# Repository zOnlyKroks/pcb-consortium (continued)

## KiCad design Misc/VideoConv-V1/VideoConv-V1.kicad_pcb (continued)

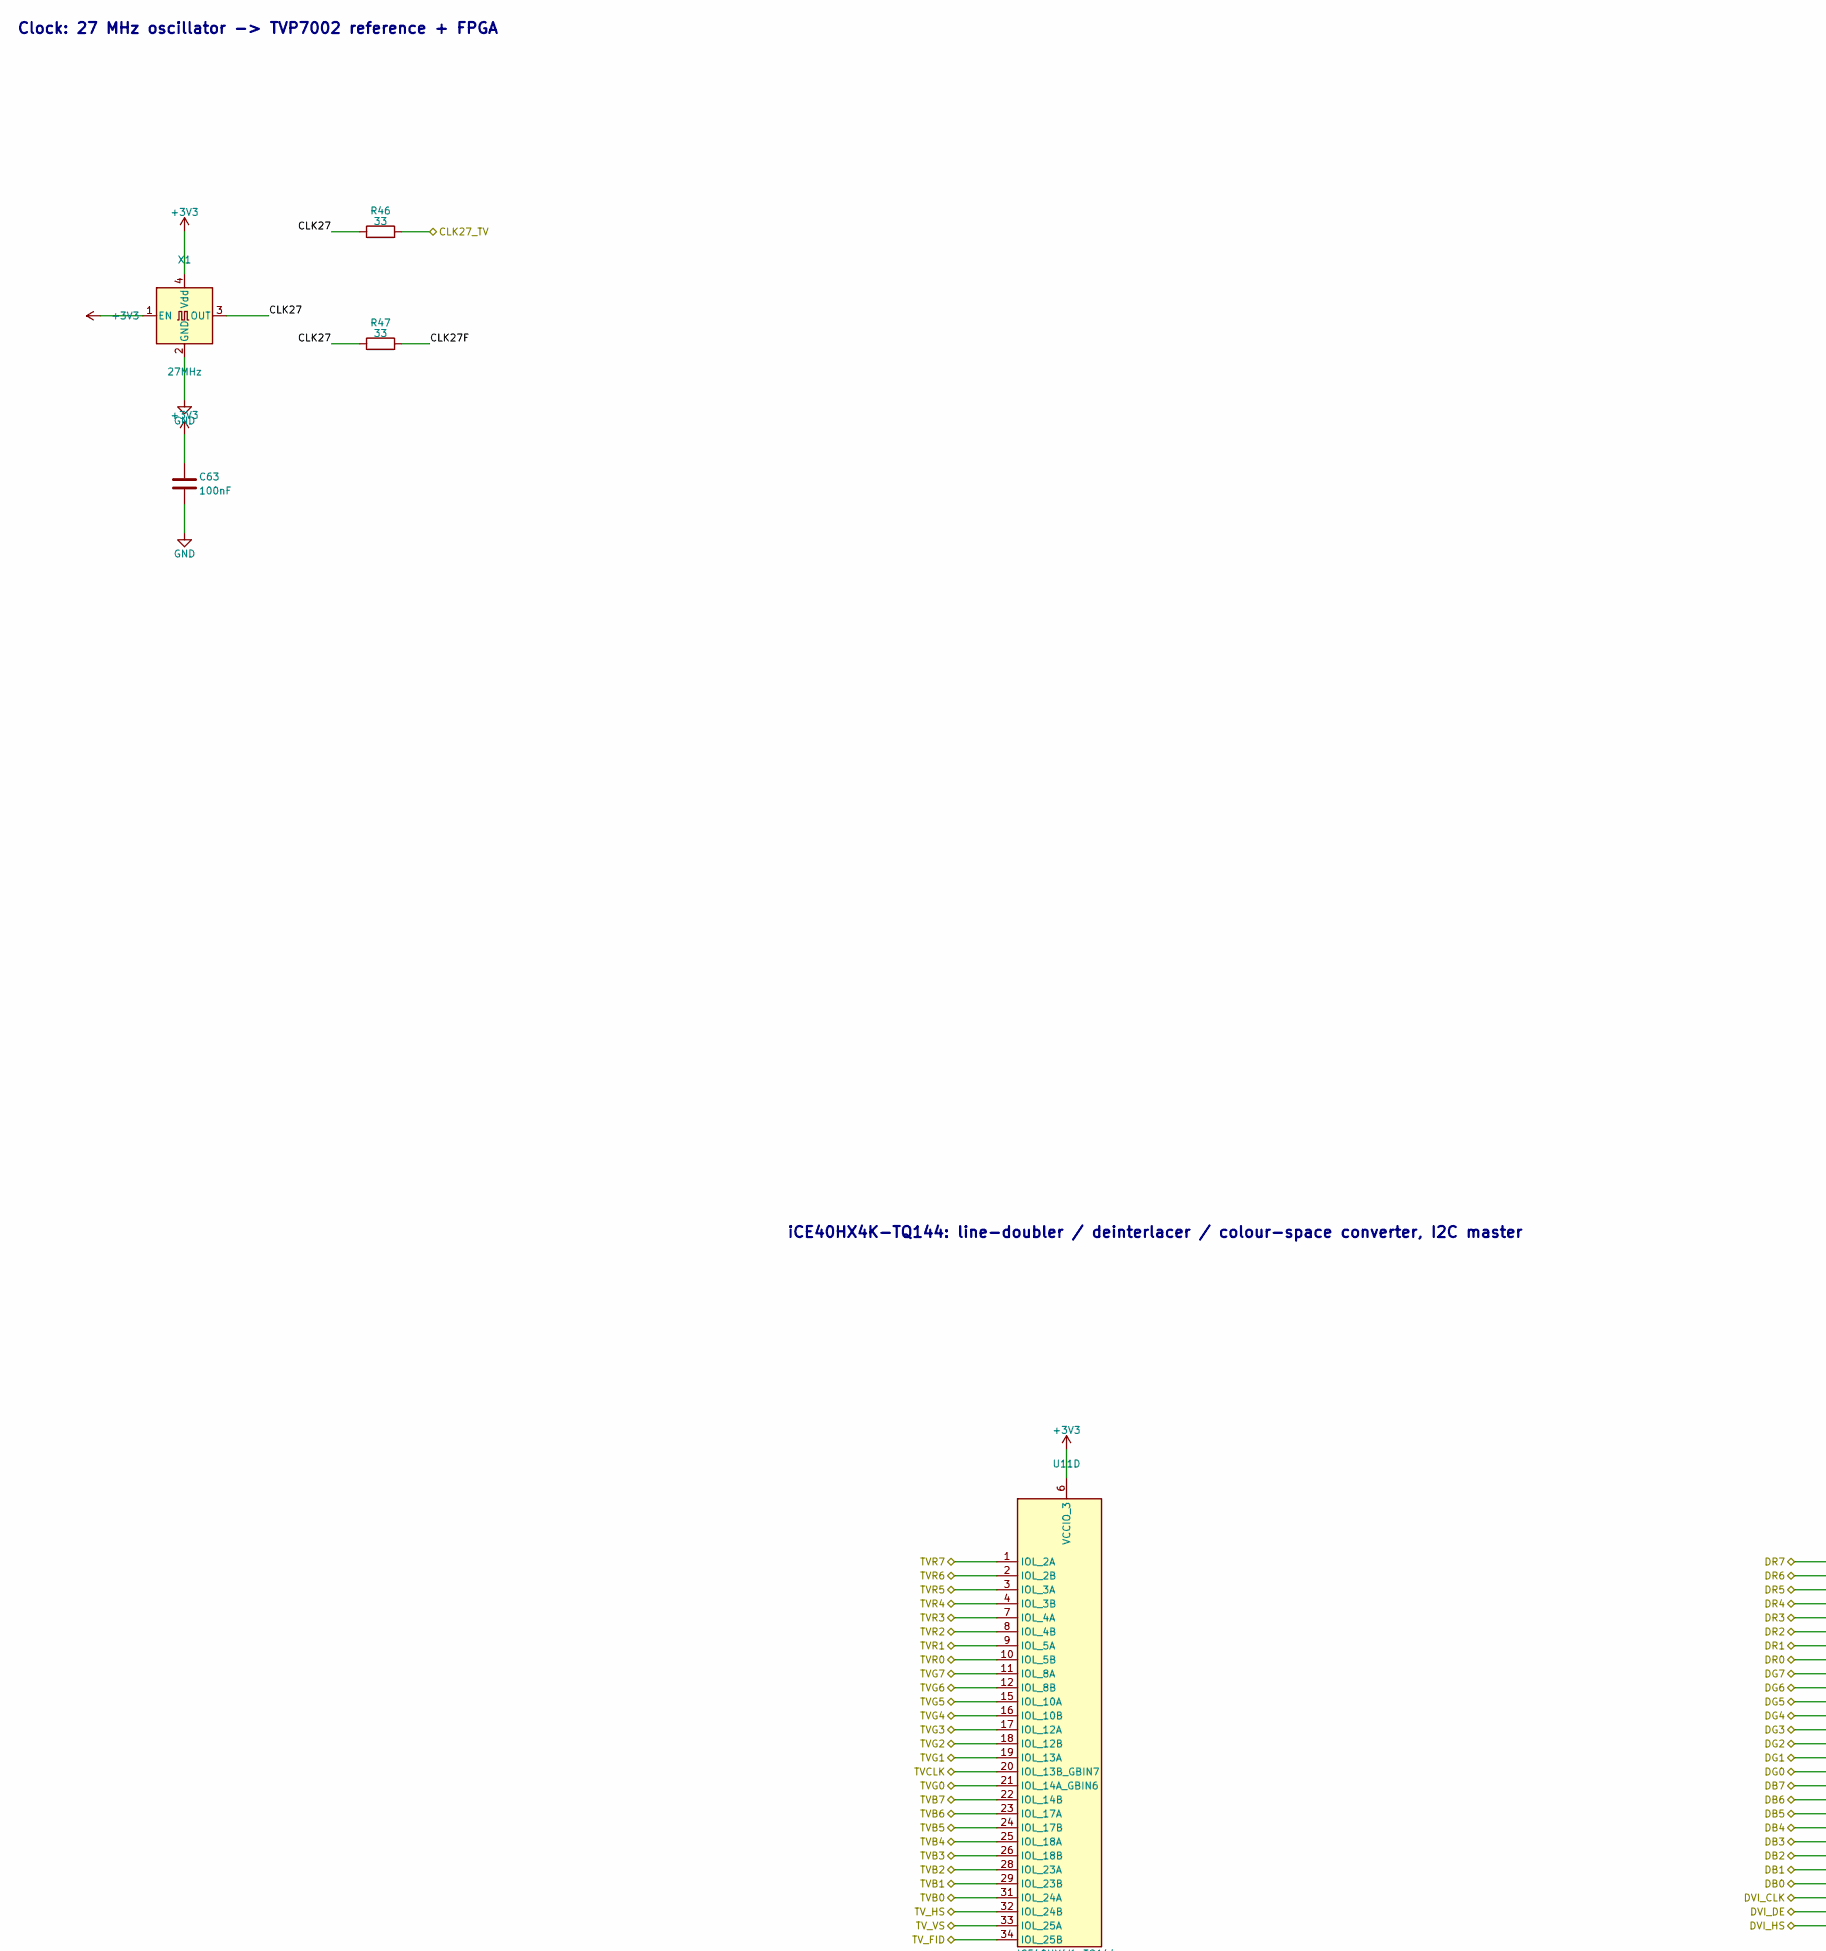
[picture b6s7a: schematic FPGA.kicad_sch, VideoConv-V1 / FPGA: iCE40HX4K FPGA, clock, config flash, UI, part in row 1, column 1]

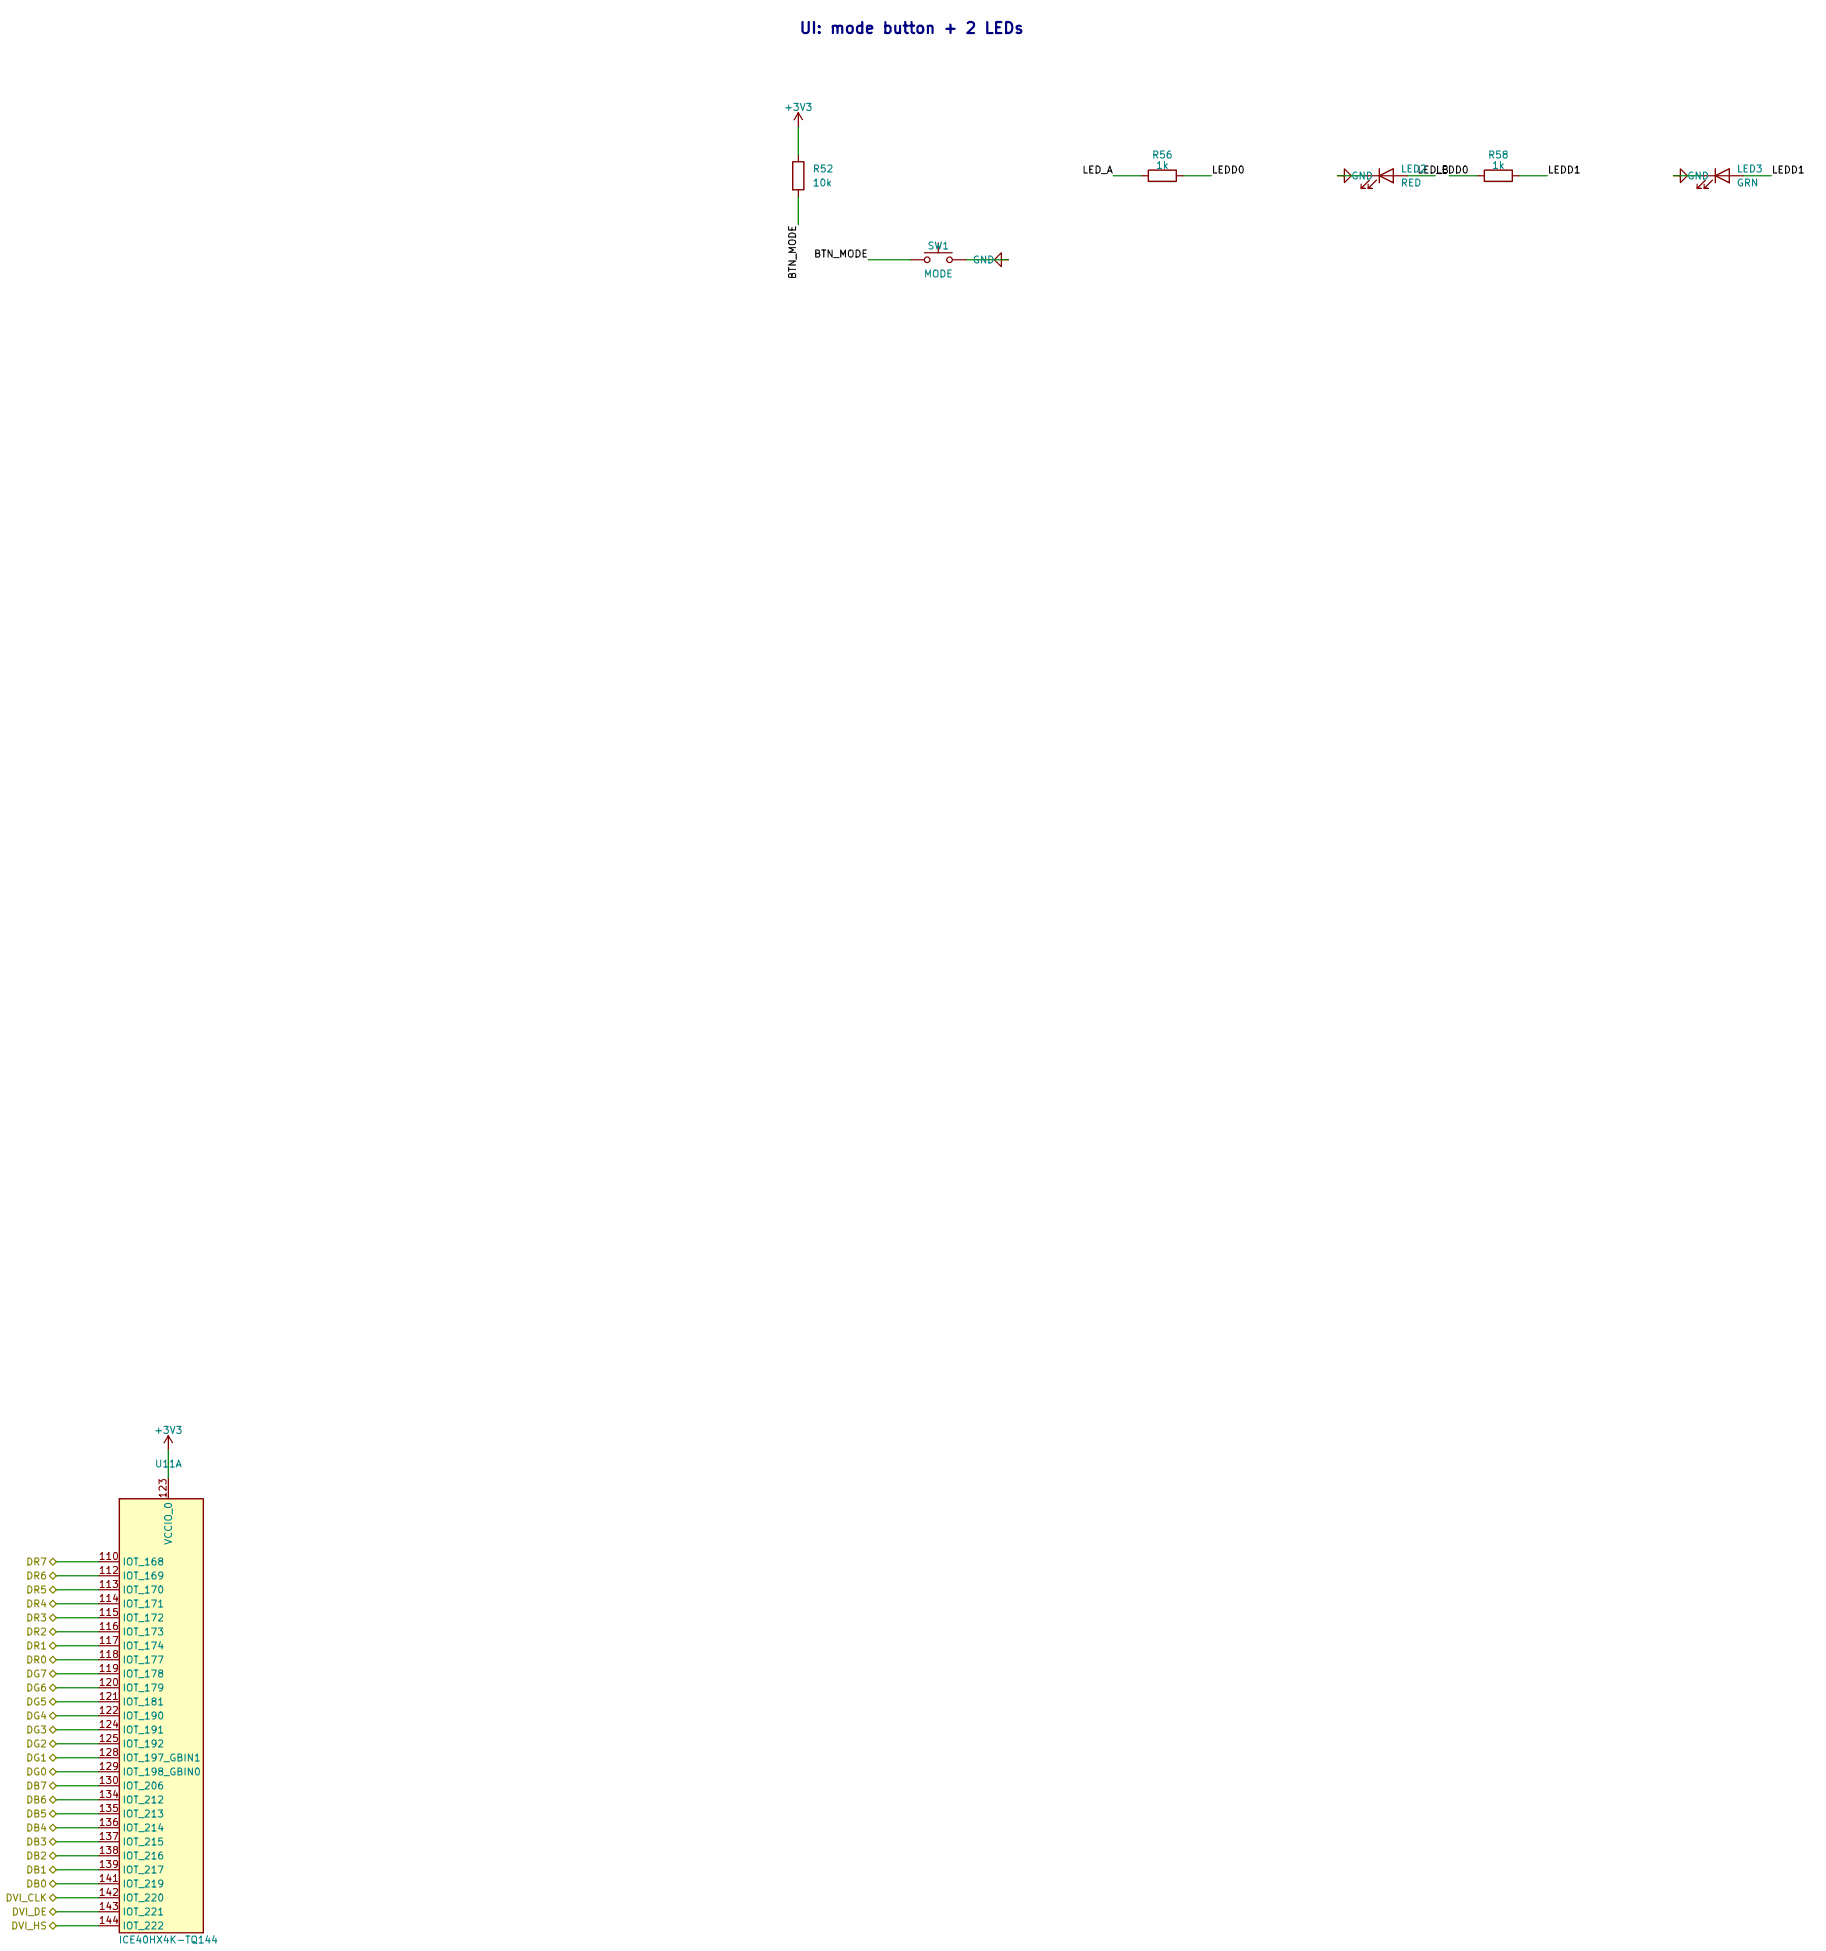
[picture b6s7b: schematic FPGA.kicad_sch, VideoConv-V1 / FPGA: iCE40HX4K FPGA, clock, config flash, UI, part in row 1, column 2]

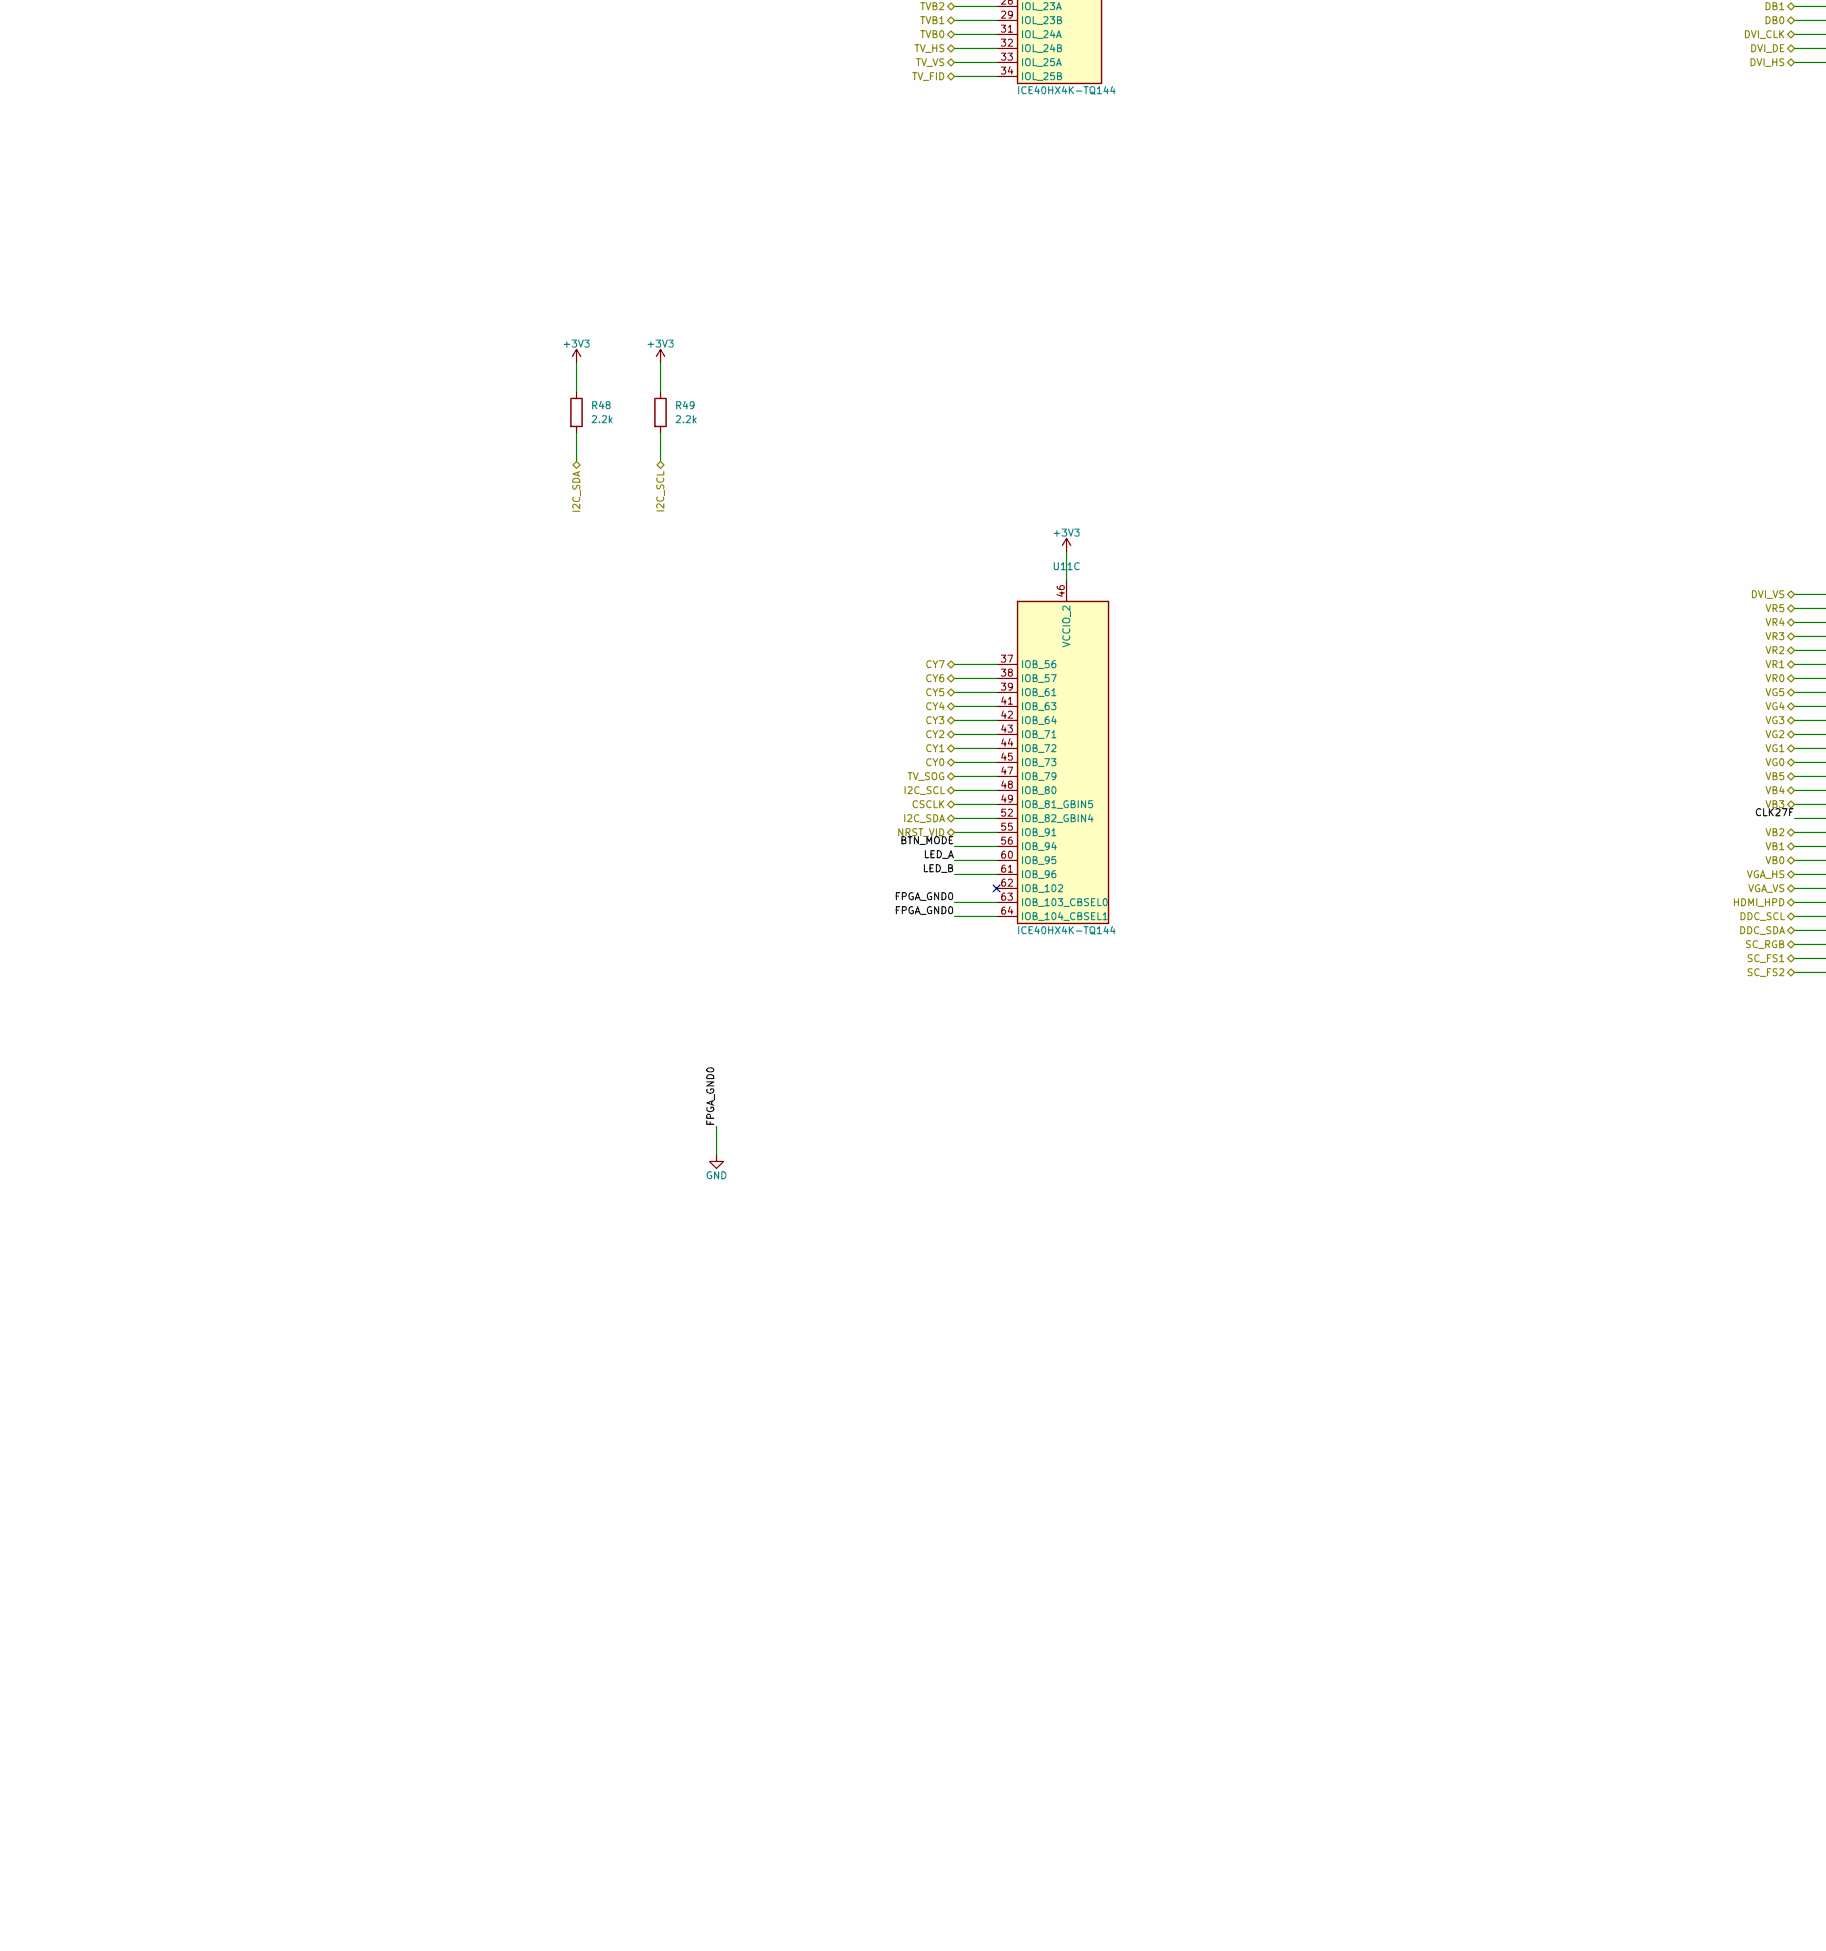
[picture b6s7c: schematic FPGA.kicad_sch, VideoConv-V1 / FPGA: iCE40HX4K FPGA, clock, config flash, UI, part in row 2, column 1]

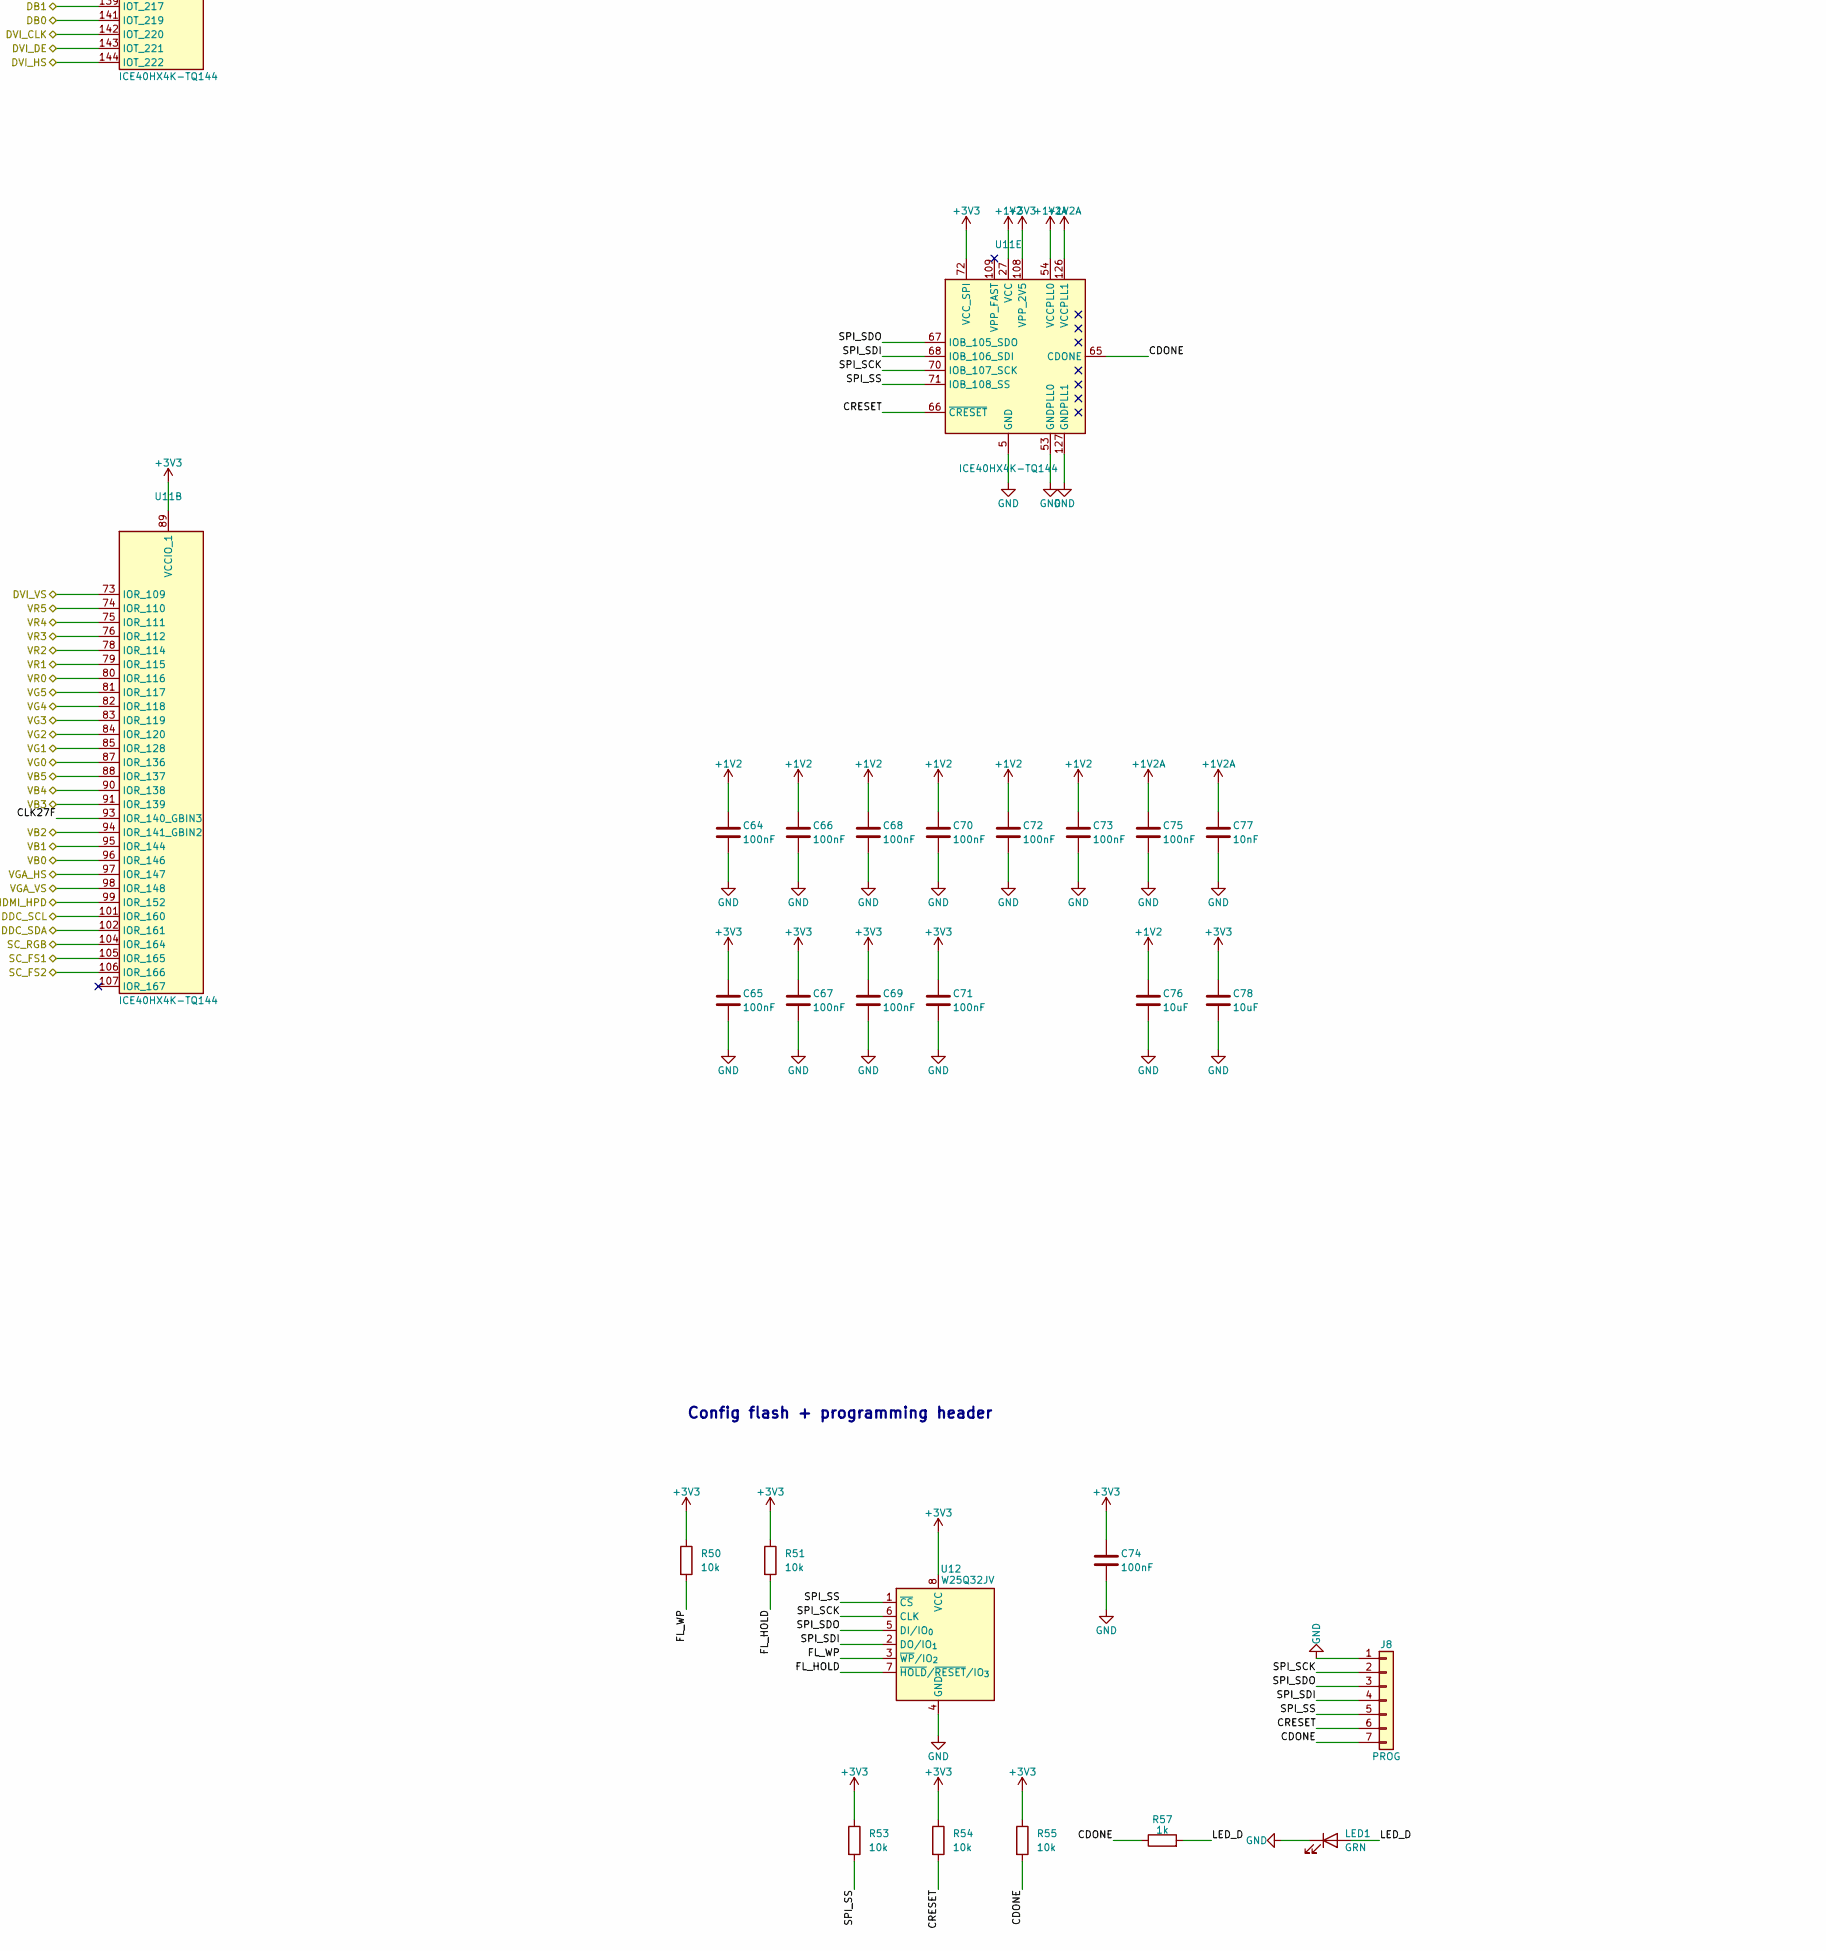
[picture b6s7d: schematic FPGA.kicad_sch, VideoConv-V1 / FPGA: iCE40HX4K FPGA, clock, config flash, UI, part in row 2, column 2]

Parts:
C63, C64, C65, C66, C67, C68, C69, C70, C71, C72, C73, C74, C75: 100nF; C_0603_1608Metric; LCSC Part # C1591
C76, C78: 10uF; C_0805_2012Metric; LCSC Part # C15850
C77: 10nF; C_0603_1608Metric; LCSC Part # C1589
J8: PROG; PinHeader_1x07_P2.54mm_Vertical; LCSC Part # C2894930
LED1, LED3: GRN; LED_0603_1608Metric; LCSC Part # C12624
LED2: RED; LED_0603_1608Metric; LCSC Part # C2286
R46, R47: 33; R_0603_1608Metric; LCSC Part # C23140
R48, R49: 2.2k; R_0603_1608Metric; LCSC Part # C4190
R50, R51, R52, R53, R54, R55: 10k; R_0603_1608Metric; LCSC Part # C25804
R56, R57, R58: 1k; R_0603_1608Metric; LCSC Part # C21190
SW1: MODE; SW_TS-1187A-B-A-B; MPN TS-1187A-B-A-B; LCSC Part # C318884
U11: ICE40HX4K-TQ144; TQFP-144_20x20mm_P0.5mm; MPN ICE40HX4K-TQ144; LCSC Part # C1521989
U12: W25Q32JV; SOIC-8_5.3x5.3mm_P1.27mm; MPN W25Q32JVSSIQ; LCSC Part # C82344
X1: 27MHz; Oscillator_SMD_Abracon_ASE-4Pin_3.2x2.5mm; MPN 27 MHz, 3.3 V, +-50 ppm; LCSC Part # C295526

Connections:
+1V2: C64.1, C66.1, C68.1, C70.1, C72.1, C73.1, C76.1, U11.27 (VCC), U11.40 (VCC), U11.92 (VCC), U11.111 (VCC); also elsewhere on the board
+1V2A: C75.1, C77.1, U11.54 (VCCPLL0), U11.126 (VCCPLL1); also elsewhere on the board
+3V3: C63.1, C65.1, C67.1, C69.1, C71.1, C74.1, C78.1, R48.1, R49.1, R50.1, R51.1, R52.1, R53.1, R54.1, R55.1, U11.6 (VCCIO_3), U11.30 (VCCIO_3), U11.46 (VCCIO_2), U11.57 (VCCIO_2), U11.72 (VCC_SPI), U11.89 (VCCIO_1), U11.100 (VCCIO_1), U11.108 (VPP_2V5), U11.123 (VCCIO_0), U11.131 (VCCIO_0), U12.8 (VCC), X1.1 (EN), X1.4 (Vdd); also elsewhere on the board
/CLK27_TV: R46.2; also elsewhere on the board
/CSCLK: U11.49 (IOB_81_GBIN5); also elsewhere on the board
/CY0: U11.45 (IOB_73); also elsewhere on the board
/CY1: U11.44 (IOB_72); also elsewhere on the board
/CY2: U11.43 (IOB_71); also elsewhere on the board
/CY3: U11.42 (IOB_64); also elsewhere on the board
/CY4: U11.41 (IOB_63); also elsewhere on the board
/CY5: U11.39 (IOB_61); also elsewhere on the board
/CY6: U11.38 (IOB_57); also elsewhere on the board
/CY7: U11.37 (IOB_56); also elsewhere on the board
/DB0: U11.141 (IOT_219); also elsewhere on the board
/DB1: U11.139 (IOT_217); also elsewhere on the board
/DB2: U11.138 (IOT_216); also elsewhere on the board
/DB3: U11.137 (IOT_215); also elsewhere on the board
/DB4: U11.136 (IOT_214); also elsewhere on the board
/DB5: U11.135 (IOT_213); also elsewhere on the board
/DB6: U11.134 (IOT_212); also elsewhere on the board
/DB7: U11.130 (IOT_206); also elsewhere on the board
/DDC_SCL: U11.101 (IOR_160); also elsewhere on the board
/DDC_SDA: U11.102 (IOR_161); also elsewhere on the board
/DG0: U11.129 (IOT_198_GBIN0); also elsewhere on the board
/DG1: U11.128 (IOT_197_GBIN1); also elsewhere on the board
/DG2: U11.125 (IOT_192); also elsewhere on the board
/DG3: U11.124 (IOT_191); also elsewhere on the board
/DG4: U11.122 (IOT_190); also elsewhere on the board
/DG5: U11.121 (IOT_181); also elsewhere on the board
/DG6: U11.120 (IOT_179); also elsewhere on the board
/DG7: U11.119 (IOT_178); also elsewhere on the board
/DR0: U11.118 (IOT_177); also elsewhere on the board
/DR1: U11.117 (IOT_174); also elsewhere on the board
/DR2: U11.116 (IOT_173); also elsewhere on the board
/DR3: U11.115 (IOT_172); also elsewhere on the board
/DR4: U11.114 (IOT_171); also elsewhere on the board
/DR5: U11.113 (IOT_170); also elsewhere on the board
/DR6: U11.112 (IOT_169); also elsewhere on the board
/DR7: U11.110 (IOT_168); also elsewhere on the board
/DVI_CLK: U11.142 (IOT_220); also elsewhere on the board
/DVI_DE: U11.143 (IOT_221); also elsewhere on the board
/DVI_HS: U11.144 (IOT_222); also elsewhere on the board
/DVI_VS: U11.73 (IOR_109); also elsewhere on the board
/FPGA/BTN_MODE: R52.2, SW1.1, U11.56 (IOB_94)
/FPGA/CDONE: J8.7, R55.2, R57.1, U11.65 (CDONE)
/FPGA/CLK27: R46.1, R47.1, X1.3 (OUT)
/FPGA/CLK27F: R47.2, U11.93 (IOR_140_GBIN3)
/FPGA/CRESET: J8.6, R54.2, U11.66 (~CRESET)
/FPGA/FL_HOLD: R51.2, U12.7 (~HOLD/~RESET/IO_{3})
/FPGA/FL_WP: R50.2, U12.3 (~WP/IO_{2})
/FPGA/LEDD0: LED2.2 (A), R56.2
/FPGA/LEDD1: LED3.2 (A), R58.2
/FPGA/LED_A: R56.1, U11.60 (IOB_95)
/FPGA/LED_B: R58.1, U11.61 (IOB_96)
/FPGA/LED_D: LED1.2 (A), R57.2
/FPGA/SPI_SCK: J8.2, U11.70 (IOB_107_SCK), U12.6 (CLK)
/FPGA/SPI_SDI: J8.4, U11.68 (IOB_106_SDI), U12.2 (DO/IO_{1})
/FPGA/SPI_SDO: J8.3, U11.67 (IOB_105_SDO), U12.5 (DI/IO_{0})
/FPGA/SPI_SS: J8.5, R53.2, U11.71 (IOB_108_SS), U12.1 (~CS)
/HDMI_HPD: U11.99 (IOR_152); also elsewhere on the board
/I2C_SCL: R49.2, U11.48 (IOB_80); also elsewhere on the board
/I2C_SDA: R48.2, U11.52 (IOB_82_GBIN4); also elsewhere on the board
/NRST_VID: U11.55 (IOB_91); also elsewhere on the board
/SC_FS1: U11.105 (IOR_165); also elsewhere on the board
/SC_FS2: U11.106 (IOR_166); also elsewhere on the board
/SC_RGB: U11.104 (IOR_164); also elsewhere on the board
/TVB0: U11.31 (IOL_24A); also elsewhere on the board
/TVB1: U11.29 (IOL_23B); also elsewhere on the board
/TVB2: U11.28 (IOL_23A); also elsewhere on the board
/TVB3: U11.26 (IOL_18B); also elsewhere on the board
/TVB4: U11.25 (IOL_18A); also elsewhere on the board
/TVB5: U11.24 (IOL_17B); also elsewhere on the board
/TVB6: U11.23 (IOL_17A); also elsewhere on the board
/TVB7: U11.22 (IOL_14B); also elsewhere on the board
/TVCLK: U11.20 (IOL_13B_GBIN7); also elsewhere on the board
/TVG0: U11.21 (IOL_14A_GBIN6); also elsewhere on the board
/TVG1: U11.19 (IOL_13A); also elsewhere on the board
/TVG2: U11.18 (IOL_12B); also elsewhere on the board
/TVG3: U11.17 (IOL_12A); also elsewhere on the board
/TVG4: U11.16 (IOL_10B); also elsewhere on the board
/TVG5: U11.15 (IOL_10A); also elsewhere on the board
/TVG6: U11.12 (IOL_8B); also elsewhere on the board
/TVG7: U11.11 (IOL_8A); also elsewhere on the board
/TVR0: U11.10 (IOL_5B); also elsewhere on the board
/TVR1: U11.9 (IOL_5A); also elsewhere on the board
/TVR2: U11.8 (IOL_4B); also elsewhere on the board
/TVR3: U11.7 (IOL_4A); also elsewhere on the board
/TVR4: U11.4 (IOL_3B); also elsewhere on the board
/TVR5: U11.3 (IOL_3A); also elsewhere on the board
/TVR6: U11.2 (IOL_2B); also elsewhere on the board
/TVR7: U11.1 (IOL_2A); also elsewhere on the board
/TV_FID: U11.34 (IOL_25B); also elsewhere on the board
/TV_HS: U11.32 (IOL_24B); also elsewhere on the board
/TV_SOG: U11.47 (IOB_79); also elsewhere on the board
/TV_VS: U11.33 (IOL_25A); also elsewhere on the board
/VB0: U11.96 (IOR_146); also elsewhere on the board
/VB1: U11.95 (IOR_144); also elsewhere on the board
/VB2: U11.94 (IOR_141_GBIN2); also elsewhere on the board
/VB3: U11.91 (IOR_139); also elsewhere on the board
/VB4: U11.90 (IOR_138); also elsewhere on the board
/VB5: U11.88 (IOR_137); also elsewhere on the board
/VG0: U11.87 (IOR_136); also elsewhere on the board
/VG1: U11.85 (IOR_128); also elsewhere on the board
/VG2: U11.84 (IOR_120); also elsewhere on the board
/VG3: U11.83 (IOR_119); also elsewhere on the board
/VG4: U11.82 (IOR_118); also elsewhere on the board
/VG5: U11.81 (IOR_117); also elsewhere on the board
/VGA_HS: U11.97 (IOR_147); also elsewhere on the board
/VGA_VS: U11.98 (IOR_148); also elsewhere on the board
/VR0: U11.80 (IOR_116); also elsewhere on the board
/VR1: U11.79 (IOR_115); also elsewhere on the board
/VR2: U11.78 (IOR_114); also elsewhere on the board
/VR3: U11.76 (IOR_112); also elsewhere on the board
/VR4: U11.75 (IOR_111); also elsewhere on the board
/VR5: U11.74 (IOR_110); also elsewhere on the board
GND: C63.2, C64.2, C65.2, C66.2, C67.2, C68.2, C69.2, C70.2, C71.2, C72.2, C73.2, C74.2, C75.2, C76.2, C77.2, C78.2, J8.1, LED1.1 (K), LED2.1 (K), LED3.1 (K), SW1.2, U11.5 (GND), U11.13 (GND), U11.14 (GND), U11.53 (GNDPLL0), U11.59 (GND), U11.63 (IOB_103_CBSEL0), U11.64 (IOB_104_CBSEL1), U11.69 (GND), U11.86 (GND), U11.103 (GND), U11.127 (GNDPLL1), U11.132 (GND), U11.140 (GND), U12.4 (GND), X1.2 (GND); also elsewhere on the board

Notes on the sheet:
UI: mode button + 2 LEDs
Clock: 27 MHz oscillator -> TVP7002 reference + FPGA
iCE40HX4K-TQ144: line-doubler / deinterlacer / colour-space converter, I2C master
Config flash + programming header
